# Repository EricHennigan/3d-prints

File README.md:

# 3d-prints
Models for 3D prints

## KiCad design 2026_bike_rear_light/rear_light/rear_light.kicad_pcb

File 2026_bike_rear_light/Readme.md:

# Parts List

| Part           | Needed | Purchased | Cost | Description                           |
|----------------|--------|-----------|------|---------------------------------------|
| IRF540N        |      3 |         5 | 3.26 | N-type Mosfet, 100V 33A               |
| LM2596HV       |      1 |         1 | 1.35 | DC-DC Buck Converter 4.5-50V to 3-35V |
| M6 4pin female |      1 |         1 | 2.53 | Cable connection                      |
| ATtiny85       |      1 |         1 | 3.37 | Microcontroller                       |
| Resistors      |      ? |       300 | 2.52 | Box of resistors                      |
| 2N2222         |      1 |        50 | 1.50 | Latch transistor                      |
| Breadbord      |      1           1 | 2.16 | MB-102 830pts Breadboard              |

# Design

Measured the LED breaklight at 75mA, so it has high-ish voltage, but little current

# 2026-06-19 First Draft

## For Controlling the light (red=on, white=brake)

```
+50V  ───── Lamp ───── Drain   IRF540N   Source ───── 0V/GND
                          |
ATtiny85 pin ── 100Ω ── Gate
                          |
                        10kΩ
                          |
                        GND
```

Note: should use a larger resistor >300Ω to limit ~20mA from ATtiny85

* https://www.instructables.com/ArduinoMicrocontroller-MOSFET/
* [Arduino IRF540 Mosfetf](https://www.youtube.com/watch?v=BPyV6fDcEiw&t=3s)

## For Controlling the power to ATtiny85 (

Power section
 * 50 V always-on input to LM2596HV IN+ / IN-.
 * LM2596HV set to 5.0 V output.
 * LM2596HV 5 V output powers the ATtiny85 VCC.
 * Common ground between 50 V source, LM2596HV, ATtiny85, and the 4.5 V trigger source.

Trigger input
 * Feed the 4.5 V signal into an ATtiny85 input pin through a series resistor, for example 10 kΩ.
 * Add a 100 kΩ pulldown on that input so it reads low when the bicycle/brake signal disappears.
 * If the 4.5 V line is noisy, add a 0.1 µF capacitor to ground for filtering.

Latch switch using IRF540N (low-side master switch for buck converter ground return)
 * 50 V supply negative goes to IRF540N drain.
 * IRF540N source goes to system ground and LM2596HV IN-.
 * ATtiny85 output drives the gate through 270 Ω.
 * Gate has a 100 kΩ pull-down to source.

When the ATtiny85 turns the MOSFET on, the LM2596HV gets its ground reference and powers up. When the ATtiny85 turns it off, the converter loses ground and the whole controller shuts down.

If your LM2596HV module has an EN pin, that is better than switching its ground. In that case:
 * Keep 50 V on the converter input all the time.
 * Use the ATtiny85 to hold EN active after startup.
 * Read the 4.5 V trigger on an input pin.
 * After 1 minute of trigger absence, drive EN inactive.
That avoids interrupting the converter ground and is cleaner if your module supports it

The most reliable version with your parts is:
 * LM2596HV makes 5 V for the ATtiny85.
 * ATtiny85 reads the 4.5 V line.
 * ATtiny85 drives the IRF540N gate.
 * IRF540N either switches the LM2596HV ground or, preferably, an enable stage if your converter module has one.

* [5 Soft Latching Power Circuits](https://www.youtube.com/watch?v=7D9L9oS4AJM&t=1s)
* https://electronics.stackexchange.com/questions/81935/mosfet-usage-and-p-vs-n-channel

```
                 +50V always-on
                      |
                      +-----------------------> LM2596HV IN+
                      |
                     GND ---------------------> LM2596HV IN-

LM2596HV OUT+ -------------------------------> ATtiny85 pin 8 (VCC)
LM2596HV OUT- -------------------------------> ATtiny85 pin 4 (GND)

4.5V trigger signal
      |
     10k
      |
      +--------------------------------------> ATtiny85 pin 7 (PB2) or pin 5 (PB0)
      |
    100k
      |
     GND
      |
    0.1uF
      |
     GND

ATtiny85 pin 6 (PB1) ---- 1k to 4.7k ----> 2N2222 base
2N2222 emitter ---------------------------> GND
2N2222 collector ---- 100Ω ----+---------> IRF540N gate
                               |
                              100k
                               |
                              GND

IRF540N source ---------------------------> GND
IRF540N drain ----------------------------> switched return node
```

# 2026-06-20 Second Draft

After looking more closely at some of the spec, and some Kicad simulation, I realized that I need different parts.
The mosfets should be a 'logical' variant, so that they can fully trigger from the 4.5v rather than a 10v signal.
The power input circuit can use a couple of diodes to act as the OR gate providing 4.5v (from bike) or 5v (from buck) to the ATtiny.
I want to turn the brakelight into an actual cable.

For development, I want a breadboard and power circuit

| Part           | Needed | Purchased | Cost | Description                     |
|----------------|--------|-----------|------|---------------------------------|
| IRL540N        |      2 |         5 | 2.41 | N-type Mosfet, 100V 33A         |
| BAT85          |      2 |        50 | 1.68 | Schottky Diode D0-35            |
| M6 5pin cable  | 1m 1f  |    1 pair | 3.04 | male & female cable pair        |
| ZY12PDN        |      1 |         1 | 2.02 | USB-C power with post terminals |
| breadboard     |      1 |         5 | 2.53 | solderable, various sizes       |

These changes obsolete some parts already purchased:
 - IRF540N, 2N2222

Also realized that I need to get some breakaway header pins + socket so the ATtiny can be removed for programming.
And KF2510 connectors + sockets to make the eBike + brake cables pluggable, board removable.

## Models

* https://github.com/yasir-shahzad/Digispark-ATTINY85
  has 3D and schematics for the board!

## More Revisions

Then I figured out that I need the circuit to be a high-side control, because the brake light has common ground.
The 2N2222 transistors are only rated for 40V, so now they are not suitable (but already purchased).
And some other parts: like flux rosin, header pins, and connector cables.

* [12v arduino high-side circuit](https://europe1.discourse-cdn.com/arduino/original/4X/a/4/9/a492336dbcc6dfbb94111606fce4d31aaf3bd7c3.jpeg)
* [48v arduino high-side circuit](https://www.reddit.com/r/AskElectronics/comments/1lqwbhb/drive_pchannel_mosfet_switching_48v_with_3v3/)

| Part              | Needed | Purchased  | Cost | Description              |
|-------------------|--------|------------|------|--------------------------|
| IRL540N           | Remove |            |      | N-type Mosfet, 100V 33A  |
| 2N5551            |      2 |         25 | 1.33 | NPN transistors (100V)   |
| FQP27P06          |      2 |         10 | 3.10 | P-Type Mosfet, -60V -27A |
| KF2510 kit        |      1 |         40 | 2.83 | connect kit for cables   |
| Female SMD socket |   9pin | 40pin * 10 | 2.82 | 2.54mm socket pins       |

## Yet More Revisions

The buck converter requires a constant HIGH signal on the "enable" pin to stay off.
Consequently, I have to make a suicide circuit to control the 48v input to the converter.
It needs another mosfet (got extras) and transistors (extras) and resistors (extras).
We no longer need the diodes!

| Part   | Needed | Purchased  | Cost | Description              |
|--------|--------|------------|------|--------------------------|
| BAT85  | Remove |            |      | Schottky Diode D0-35     |

# 2026-06-21

Found a KiCAD model for the ATtiny
 * [swww1235](https://github.com/sww1235/KiCAD-Libraries/tree/master/SW-Digistump.pretty)

# 2026-07-02

## Software

Attempted to use a snap package
 - wants 32 bit libs during compilation step.
Attempted to use a deb package
 - could not install, don't know why
Attempted to use the official digistump package
 - but the micronucleus is too old (cannot locate device on usb)

Fortunately, is easy to clear state by `rm -rf ~/.arduino15`

Install
```
wget https://github.com/arduino/arduino-cli/releases/download/v1.5.1/arduino-cli_1.5.1-1_amd64.deb
sudo apt install ./arduino-cli_1.5.1-1_amd64.deb
sudo apt install libusb-1.0-0-dev # for the newer micronucleus
```

Setup (had to pick a version with modern micronucleus)
```
old_url="https://raw.githubusercontent.com/digistump/arduino-boards-index/master/package_digistump_index.json"
url="https://raw.githubusercontent.com/ArminJo/DigistumpArduino/master/package_digistump_index.json"
arduino-cli config set board_manager.additional_urls $url
arduino-cli core update-index
arduino-cli core install digistump:avr
```

Additional Steps: Did not know about the usb assignment
```
Copy https://github.com/micronucleus/micronucleus/blob/master/commandline/49-micronucleus.rules
To /etc/udev/rules.d
sudo udevadm control --reload-rules
```

Arduino expects that the code file is a dir of the same name.

Program, `cd code`
Do not plug it in until prompted by the 'upload' step
```
arduino-cli compile --fqbn digistump:avr:digispark-tiny code.ino
arduino-cli upload --fqbn digistump:avr:digispark-tiny code.ino
```

# 2026-07-16 Circuit Debugging, Broken ATtiny

Was trying to debug the circuit and made some important discoveries:
 - I thought that the VIN

Some of the pins are not available for me to use as a sensor. Specifically, I
cannot have anything on PB5, because that's the RESET pin for the ATTiny. It
won't boot (will be held in reset) if it senses anything.

So new wiring:

| Pin | Code | Purpose |
|-----|------|---------|
|  6  | PB5  | Unused - leave disconnected so chip can boot |
|  5  | PB4  | PWR_CONTROL - drives the power input transistor Q6 |
|  4  | PB3  | Unused - leave disconnected to avoid the 1.5k USB pull-up resistor conflict |
|  3  | PB2  | BRAKE_LIGHT |
|  2  | PB1  | TAIL_LIGHT |
|  1  | PB0  | SYS_PWR_READ - reads the brake line via 10k resistor |

Also I think I broke the chip by over-voltaging it. The board has its own power
regulator, but I was really confused about which pin that would be. I supplied
7.5v to the Vin pin of the ATTiny (online it said to use between 7v and 12v).

To avoid burning out the ATTiny in the future check:
1. "Resistance-to-Rail"
   power off, no chip
   measure PB4 to BATT, expect: open loop
   measure PB4 to SYS, expect: open loop
   measure PB4 to Mosfet Q4 (pwr control), expect: R9+R7+R6 (high resistance)
2. "Inline Current Limiting"
   power off, no chip
   confirm 10k R9 sits between PB4 and transistor Q6 base
   measure PB4 to base of Q6, expect: 10k
3. "Safe Simulation"
   power on, no chip
   measure volts on PB4, expect: 0v (because no driver)
   pull up test, connect PB4 to 5v with 10k resistor
     should activate Q6, Q5, Q4, turning on SYS power
   measure current flowing through tmp resistor or check that PB4 stays stable near 5v
4. "Code Safety Rule"
   always declare pin mode as OUTPUT, before attempting any digitalWrite
   avoid rapid toggling at boot in setup(), wait a sec for USB handshake to finish

Consider setting PB4 mode as INPUT_PULLUP, expecting the brake to override it

# 2026-07-26 Box Design

Major PITA.
Also, did not leave enough room for the ATTiny. Ugh!
So used the entire! day redrawing the box and lid

# 2026-08-01 Assembly on the bike

I got the brake & tail lights wired in wrong.
Swapping the pins on the molex worked.

It sparks when I plug it in. After that it doesn't turn off.

# 2026-08-02 Circuit Adjustments

At lower voltages, ~20v the circuit operates as expected.
But then at higher voltages, ~50v BATT, it fries the mosfet.

Attempted to put a zener diode across the Gate & Source, but that did not work.
I think that we can use the enable/disable pin on the buck converter instead.
Worked with Gemini to come up with a new circuit for that.

# 2026-08-04 Buck Converter Failed

After much investigation at CrashSpace today. It turns out the DC-DC Buck
Converter that I got does not handle the high input voltages, even though I got
the HVS version. Could be a cheap clone?  I'll have to look into a new circuit
design to accommodate a different Buck Converter (e.g.: a B560C has inverted
logic for the enable/disable pin).

# 2026-08-08 Rewire Circuit for new Buck Converter

Bought a HT7886 DC-DC converter, because rated at 100V input (beyond what I need)
 - Implemented a new KiCad symbol for it
 - Drew a footprint for it
 - Gemini conversation to update the schematic (because EN high == on)

Due to redesign, I need a ~5v zener diode. Hope that crash has one.

# 2026-08-15 Recieved the new DC-DC converter

- Checked that it behaves as expected, does not turn on at up to 60v
- Also checked output with an oscilloscope, very stable at 5v
- De-soldered previous circuit
- Soldered in parts new circuit
  - Check Crashspace diodes were suitable (got lucky!)
  - Used breadboard to verify behavior (it works!)
  Did not solder all the connections, it was already 4hrs work, got tired

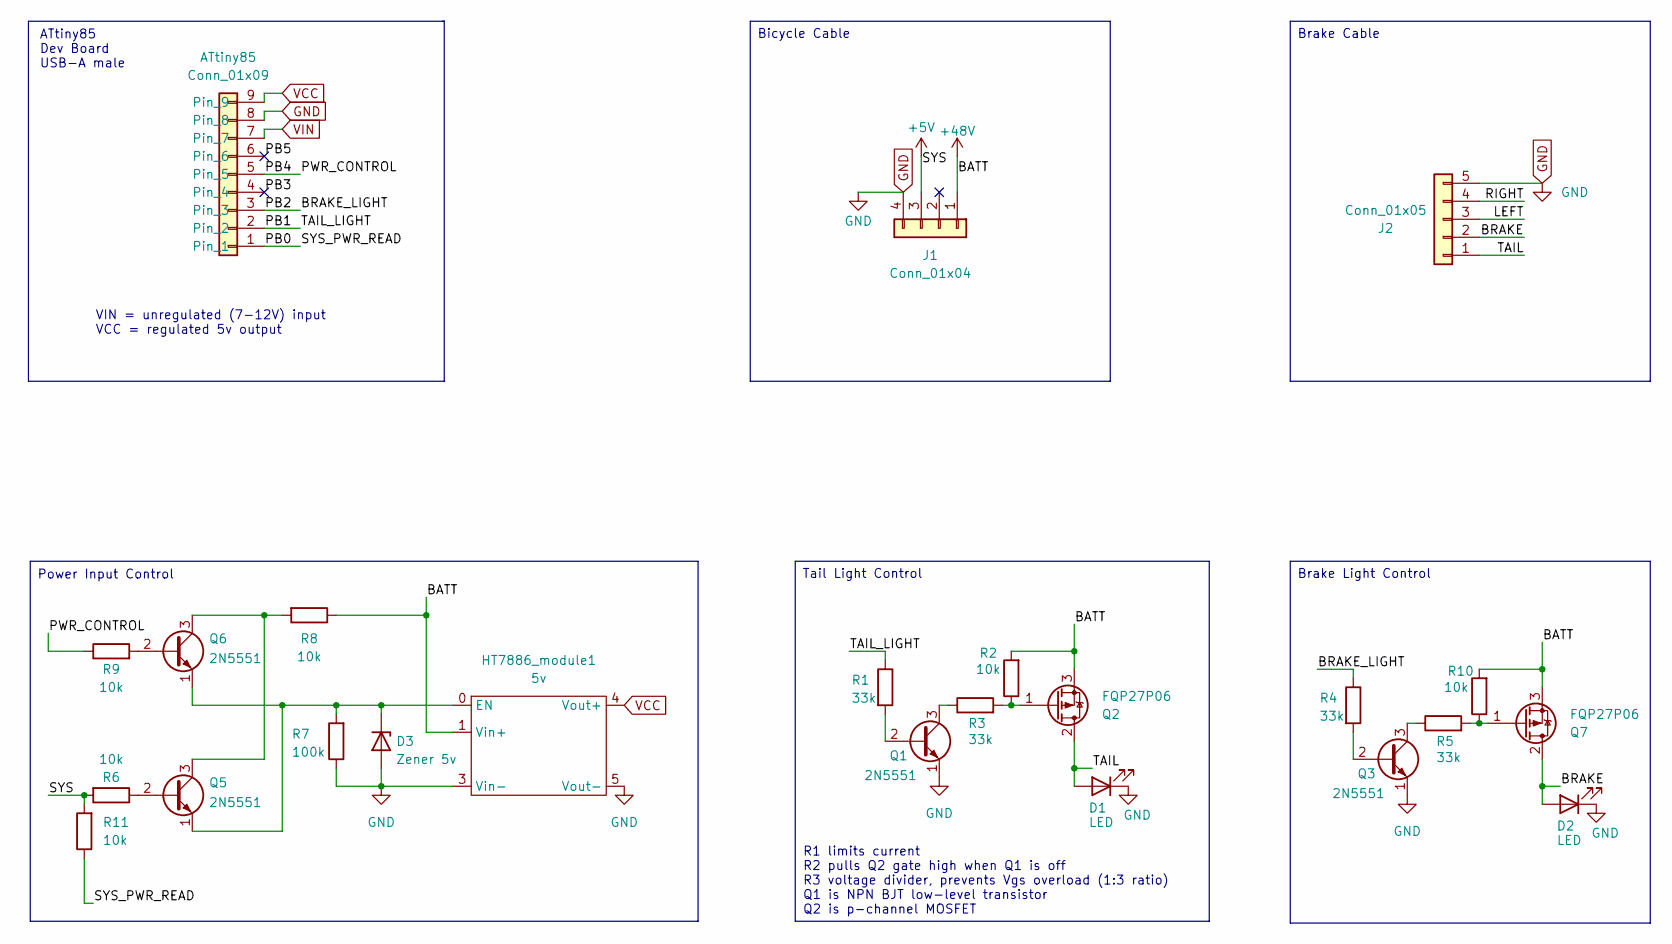
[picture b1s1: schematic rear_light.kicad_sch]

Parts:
ATtiny85: Conn_01x09; Digispark
D1, D2: LED; LED_D3.0mm
D3: Zener 5v; D_DO-41_SOD81_P10.16mm_Horizontal
HT7886_module1: 5v; DC-DC_100V_3.5A_step_down
J1: Conn_01x04; Molex_KK-254_AE-6410-04A_1x04_P2.54mm_Vertical
J2: Conn_01x05; Molex_KK-254_AE-6410-05A_1x05_P2.54mm_Vertical
Q1, Q3, Q5, Q6: 2N5551; TO-92_Inline
Q2, Q7: FQP27P06; TO-220-3_Vertical
R1, R4: 33k; R_Axial_DIN0207_L6.3mm_D2.5mm_P5.08mm_Vertical
R2, R10: 10k; R_Axial_DIN0207_L6.3mm_D2.5mm_P5.08mm_Vertical
R3, R5: 33k; R_Axial_DIN0207_L6.3mm_D2.5mm_P7.62mm_Horizontal
R6, R8, R9, R11: 10k; R_Axial_DIN0207_L6.3mm_D2.5mm_P7.62mm_Horizontal
R7: 100k; R_Axial_DIN0207_L6.3mm_D2.5mm_P7.62mm_Horizontal

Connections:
+5V: J1.3, R6.2, R11.2
+48V: HT7886_module1.1 (Vin+), J1.1, Q2.3 (S), Q7.3 (S), R2.2, R8.1, R10.2
/BRAKE: D2.2 (A), J2.2, Q7.2 (D)
/BRAKE_LIGHT: ATtiny85.3, R4.1
/LEFT: J2.3
/PB0: ATtiny85.1, R11.1
/PB1: ATtiny85.2, R1.1
/PB3: ATtiny85.4
/PB4: ATtiny85.5, R9.1
/PB5: ATtiny85.6
/RIGHT: J2.4
/TAIL: D1.2 (A), J2.1, Q2.2 (D)
GND: ATtiny85.8, D1.1 (K), D2.1 (K), D3.2 (A), HT7886_module1.3 (Vin-), HT7886_module1.5 (Vout-), J1.4, J2.5, Q1.1 (E), Q3.1 (E), R7.1
unnamed: D3.1 (K), HT7886_module1.0 (EN), Q5.1 (E), Q6.1 (E), R7.2
unnamed: Q1.2 (B), R1.2
unnamed: Q1.3 (C), R3.1
unnamed: Q2.1 (G), R2.1, R3.2
unnamed: Q3.2 (B), R4.2
unnamed: Q3.3 (C), R5.1
unnamed: Q5.2 (B), R6.1
unnamed: Q5.3 (C), Q6.3 (C), R8.2
unnamed: Q6.2 (B), R9.2
unnamed: Q7.1 (G), R5.2, R10.1
VCC: ATtiny85.9, HT7886_module1.4 (Vout+)
VIN: ATtiny85.7

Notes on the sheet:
R1 limits current R2 pulls Q2 gate high when Q1 is off R3 voltage divider, prevents Vgs overload (1:3 ratio) Q1 is NPN BJT low-level transistor Q2 is p-channel MOSFET
ATtiny85 Dev Board USB-A male
VIN = unregulated (7-12V) input VCC = regulated 5v output
Power Input Control
Brake Light Control
Brake Cable
Bicycle Cable
Tail Light Control

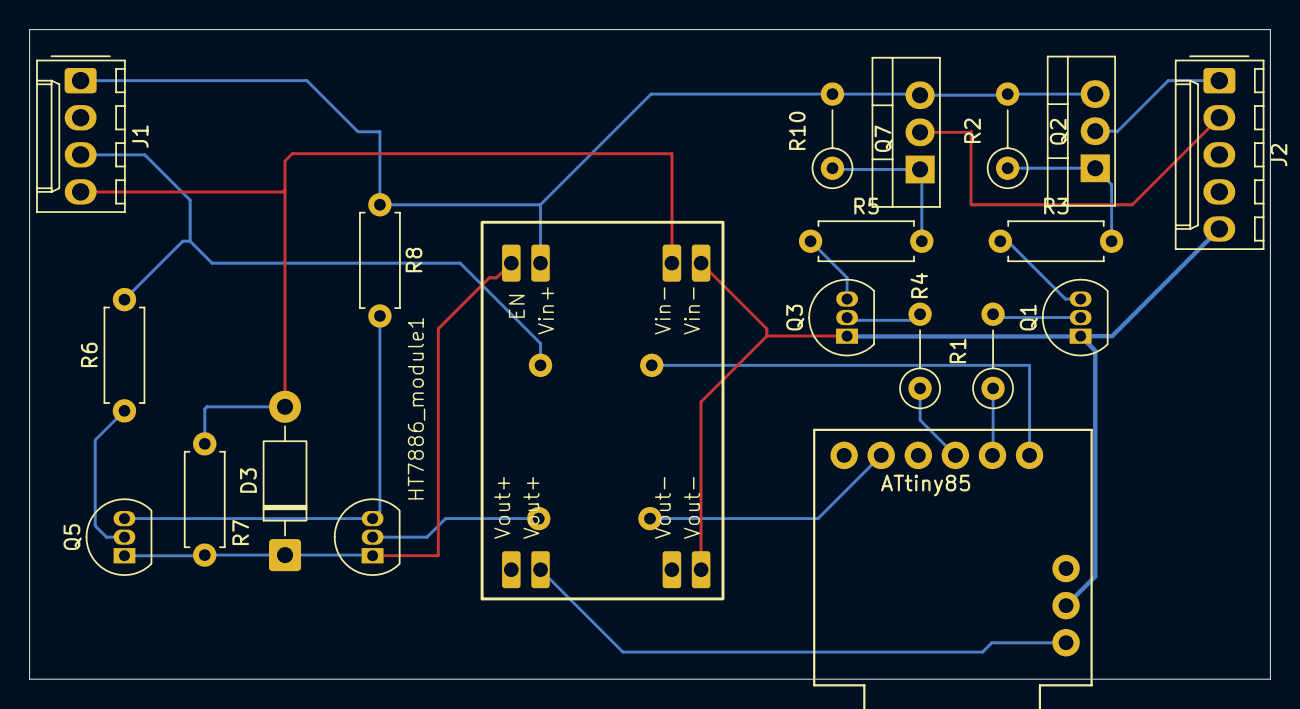
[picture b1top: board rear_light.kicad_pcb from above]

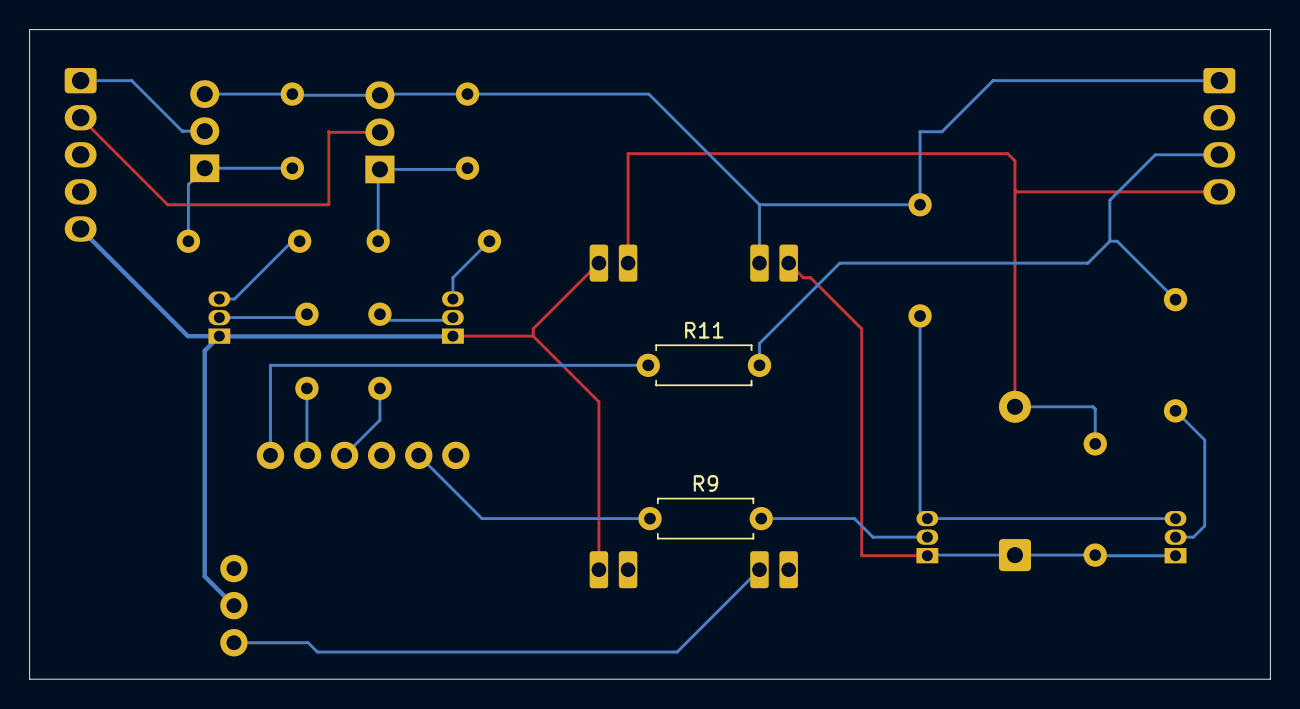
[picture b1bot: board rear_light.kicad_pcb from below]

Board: 2 copper layers, 85.0 x 44.5 mm, 22 parts (2 on the bottom side), 20 nets.

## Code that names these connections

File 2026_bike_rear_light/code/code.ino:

// Pin assignments                Digispark silkscreen labels
const int PIN_BRAKE_SENSE = PB0; // brake input (LOW = engaged)
const int PIN_LED         = PB1;
const int PIN_TAIL_LIGHT  = PB1; // tail light output
const int PIN_BRAKE_LIGHT = PB2; // brake light output
const int PIN_POWER       = PB4; // power control


// TESTING
/*
void setup() {
  pinMode(PIN_BRAKE_SENSE, INPUT);
  pinMode(PIN_TAIL_LIGHT, OUTPUT);
  pinMode(PIN_BRAKE_LIGHT, OUTPUT);
  pinMode(PIN_POWER, OUTPUT);

  digitalWrite(PIN_POWER, HIGH);
}

void loop() {
  static int counter = 0;
  counter++;
  if (counter > 30) digitalWrite(PIN_POWER, LOW);

  bool braking = (digitalRead(PIN_BRAKE_SENSE) == LOW);
  pinMode(PIN_BRAKE_LIGHT, braking);

  delay(1500);
}
*/

// DESIRED BRAKE PROGRAM

// Timing
const unsigned long POLL_INTERVAL_MS = 20; // 50Hz
const unsigned long BRAKE_TIMEOUT_MS = 60000UL; // 1 minute
unsigned long shutDownTime = 0;

void setup() {
 shutDownTime = millis() + BRAKE_TIMEOUT_MS;

 pinMode(PIN_TAIL_LIGHT,  OUTPUT);
 pinMode(PIN_BRAKE_LIGHT, OUTPUT);
 pinMode(PIN_BRAKE_SENSE, INPUT);
 pinMode(PIN_POWER,       OUTPUT);

 // Set initial lights and toggle power state
 digitalWrite(PIN_TAIL_LIGHT, HIGH);
 digitalWrite(PIN_BRAKE_LIGHT, LOW);
 digitalWrite(PIN_POWER, HIGH);
}


void loop() {
  bool braking = (digitalRead(PIN_BRAKE_SENSE) == LOW);

  // update the brake light
  digitalWrite(PIN_BRAKE_LIGHT, braking);

  // system has been shut off (or break engaged for too long)
  if (braking && millis() > shutDownTime) {
    digitalWrite(PIN_POWER, LOW);
  }

  // brake released, delay the system shutoff
  if (!braking) {
    shutDownTime = millis() + BRAKE_TIMEOUT_MS;
  }

  delay(POLL_INTERVAL_MS);
}

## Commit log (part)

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2025-08-03 Add scad file for an OpenGrid snap (lite version)
2025-08-05 Add diamine ink shelf
    - Rotate the snap so it uses "top" and "bottom"
    - Migrate global variables into a lib.scad
    - Add a diamine-shelf module
2025-08-05 Update .gitignore
    - Ignore generated stl, 3mf, and json files
2025-08-06 Add a clip snap to hold the top of the ink bottle
    - Update the snap to parameterize the nub_direction
    - Raise the wall on the shelf, so bottle sits more securely
    - Clip comes in two parts: snap and clip, for strength from layer lines
2025-08-07 Lower the position of the clip on the snap
    - Shuffle part diff and union geometry so it's fewer steps
2025-08-08 Thicken the back of the cap clip
    Prototype revealed it's pretty easy to break the connection between the
    sides of the clip when inserting it into the mount.
2025-08-13 First revision of grid with tile cutouts
    - Organized so that grid is a large box with cutouts applied
2025-08-14 Simplify the creation of the cut_tile - make it more functional with only a single call to skin()
2025-08-14 Add Chamfers to grid
    - add anchoring to grid
    - cache rendering of cut_tile for performance
2025-08-14 Add a lite_connector
    - put debug call at end of each module
2025-08-15 Add connector sockets to board
    - Create a cut_connector tool
    - Add connector sockets to the board
    - Update variables 'chamfers' and 'connectors' to arrays
2025-08-15 Adjust the z-offset of the connector sockets
2025-08-15 Fix bug with connectors on left
2025-08-16 Organize File Structure
    - Create a connectors.scad and move lite_connector into it
    - Create a directory for the diamine ink cabinet
    - Move the diamine ink shelf into the ink cabinet dir
    - Remove lib.scad and copy varible settings content into snap.scad
    - Export variables from grid.scad into grid_vars.scad
2025-08-16 Add code for making the cabinet
    - Model a generic piece with toggled borders
2025-08-16 Add padding to the back frame
    - Because the front doors have a inner wall thickness where they meet
2025-08-16 Refactor framing of cabinet
    - A single piece can operate as center, edge, or corner
    - Added doors to the cabinet
2025-08-21 Add ability to explode the cabinet into parts for printing
2025-08-21 Add hinges to the cabinet
    - re-code the back pieces to mirror, so that hinges match up
2025-08-21 Add Bill of Material support
    - Just printing out the lines of the parts
2025-08-23 Add corner-onlay to the cabinet
    - Also include some edited image files
2025-08-23 Add gemini-generated source images
2025-08-23 Increase filament diameter in hinge
2025-08-23 Increase depth of the corner onlay
2025-08-23 Add holes for magnet placement
2025-08-25 Add source imagery of the nib onlay
2025-08-25 Create an svg for the nib onlay
2025-08-25 Add the nib onlay to the front doors
    - Carves an outline first
    - Adds back the nib onlay shapes
2025-08-26 Move grids into door
    - Best way to get the same finger hole cutout of the grid
2025-09-01 Update svg onlay images
    - make sure that each image layer (object) does not overlap with others
    - simplify paths by removing duplicate (on top of each other) points
2025-09-01 Update onlay application
    - Remove piece.onlay parameter (that cuts a block)
    - Move onlays to the door module
    - Each onlay image has an "Outline" for cutting
2025-09-01 Add padding to OpenGrid
    - Add a black fill buffer around the edges
2025-09-01 Add padding to the cabinet back
    - Make sure the interior and the grid align their size
2025-09-01 Add a recess in cabinet edges for the grid
    - give the grid some clearance to fit
2025-09-01 Add recess for magnets
    - magnets to hold the front doors closed
2025-09-01 Rotate parts for printability
    - have to make sure the front door (with onlays) is face down
2025-09-02 Adjust top wall of piece so not extend into hinge
    - Only made adjustment needed for the print
2025-09-02 Give the cabinet more depth
    - it needs to hold at least an ink bottle shelf
2025-09-04 Adjustments for printing
    - Move the grids so they don't intersect cabinet (separate pieces)
    - Move the onlay into the piece, avoids separate pieces in slicer
2025-09-05 Give the cabinet more depth
    - previously forgot to account for the opengrid tile thickness
2025-09-28 Add butterfly connectors
    - Also add the grid connector piece
    - And a chamfer on the bottom of piece to prevent elephant foot
2025-09-29 Add model for clamp connector
    - Includes stl and 3mf
2025-09-29 Remove extra variables from clamp_connector
2025-10-05 First prototype for Philips Hue mount on rocker switch
2025-10-05 Download fillet gauge templates
2025-10-13 [b123d] Create a TraptailJoin
    - The traptail join is a self-centering non-locking dovetail join
2025-10-26 [b123d] Add ability to invert the TraptailJoin
    - make it easier to create a mirror image for the other side of a cut
2025-10-26 [b123d] Add init files to b123d_parts
    - So that the directories can be imported as modules
2025-10-27 [b123d] Add `cut` convenience function for cutting a part
    - Also automatically adds an interface on the cut to join the parts
2025-10-27 [b123d] Add BoxJoin
    - A join type made of straight combs, for corners and faces
    - also organize imports in traptail
2025-10-30 Finish philips hue project
    - adjustments to get a better fit over the socket
    - assertions for the dimension of various parts
    - saving the final results 3mf project
2025-12-12 Add README for philips hue wallplate (and stl models)
2026-02-01 Add Standing Desk parts
    - CableSpool for motor cables
    - ControllerPlate to hold the controller box
2026-02-07 Add Framework desktop tiles project with placeholder model and readme
2026-02-07 Adjustments to model - fillets and clips
2026-02-07 Rework model for 3x3 tile, embed the neural-net SVG
2026-02-08 Remove test STL, refresh 3MF export, document Inkscape workflow (model unchanged)
2026-06-24 Tweaks to the Philips Hue and print for single gang plate
2026-06-24 Bike Rear Light - pcb layout
2026-06-24 Update bicycle brake light for high-side switching.
2026-06-24 Rear Bike Light - Update schematic and PBC layout - Remove the older brake light circuit - Layout the PCB components (roughly)
2026-06-24 Bicycle rear light - SPICE models and Readme
